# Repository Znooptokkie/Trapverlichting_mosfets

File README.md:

# Automatische trapverlichting

Een automatisch trapverlichtingssysteem op basis van een Raspberry Pi Pico 2 en MicroPython. Het systeem gebruikt twee PIR-bewegingssensoren om beweging te detecteren en stuurt drie dimbare lampen aan via PWM.

De lampen gaan geleidelijk aan en uit. De volgorde waarin de lampen aangaan, is afhankelijk van welke sensor beweging detecteert.

## Functionaliteiten

- Automatische verlichting met twee bewegingssensoren.
- Aansturing van drie afzonderlijke lampen.
- Geleidelijke in- en uitschakeling met PWM.
- Lampen gaan met een instelbare vertraging achter elkaar aan.
- Verschillende inschakelvolgordes afhankelijk van de geactiveerde sensor.
- Instelbare brandduur op maximale helderheid.

## Hardware

- Raspberry Pi Pico 2
- 2x HC-SR505 PIR-bewegingssensor
- 3x dimbare 24V-lamp
- Mean Well LRS-100-24 voeding
- DC-DC buckconverter
- 3x N-kanaal-MOSFET
- Gateweerstanden en pull-downweerstanden
- Zekering en aansluitmateriaal

Zie [hardware.md](hardware.md) voor de onderdelenlijst en [wiring.md](wiring.md) voor de aansluitingen.

## Software

Het project maakt gebruik van MicroPython.

- `main.py`: start het programma en schakelt de lampen uit wanneer het programma handmatig wordt gestopt.
- `lamps.py`: configureert de sensoren en PWM-uitgangen en regelt de verlichting.

## Instellingen

De belangrijkste instellingen staan in `lamps.py`.

| Instelling | Betekenis | Huidige waarde |
|---|---|---:|
| `STEP` | Helderheidsstap per iteratie | 500 |
| `KEEP_SECS_ON` | Brandduur op maximale helderheid | 20 seconden |
| PWM-frequentie | Frequentie van het PWM-signaal | 1000 Hz |
| Fade-interval | Wachttijd tussen helderheidsstappen | 0,025 seconden |
| Sensorinterval | Wachttijd tussen controles | 0,01 seconden |

## Werking

### Sensor 1

1. Sensor 1 detecteert beweging.
2. Lamp 1 gaat als eerste aan, gevolgd door lamp 2 en lamp 3.
3. De lampen blijven gedurende de ingestelde tijd op maximale helderheid branden.
4. Alle lampen dimmen geleidelijk uit.

### Sensor 2

1. Sensor 2 detecteert beweging.
2. Lamp 3 gaat als eerste aan, gevolgd door lamp 2 en lamp 1.
3. De lampen blijven gedurende de ingestelde tijd op maximale helderheid branden.
4. Alle lampen dimmen geleidelijk uit.

Tijdens een actieve verlichtingscyclus worden beide sensoren tijdelijk niet opnieuw uitgelezen. Nieuwe beweging wordt daardoor genegeerd totdat de cyclus is afgelopen.

## GPIO-aansluitingen

| Onderdeel | GPIO |
|---|---|
| Bewegingssensor 1 | GP16 |
| Bewegingssensor 2 | GP22 |
| Lamp 1 | GP18 |
| Lamp 2 | GP19 |
| Lamp 3 | GP20 |

## Documentatie en PCB

De map `docs/images/` bevat afbeeldingen van het hardwareontwerp en de PCB.

- `docs/images/mosfet_pico_schema.png`: afbeelding van het elektrische schema.
- `docs/images/mosfet_pico_pcb.png`: afbeelding van de PCB-layout.
- `docs/images/mosfet_pico_3d.png`: 3D-weergave van de PCB.

De oorspronkelijke KiCad-projectbestanden staan in `hardware/kicad/`:

- `hardware/kicad/mosfet_pico.kicad_pro`: projectinstellingen.
- `hardware/kicad/mosfet_pico.kicad_sch`: elektrisch schema.
- `hardware/kicad/mosfet_pico.kicad_pcb`: PCB-ontwerp.

De Gerber-bestanden staan in `hardware/production/`. Deze bestanden kunnen worden gebruikt om de PCB bij een PCB-fabrikant te laten produceren.

## Bekende aandachtspunten

De sensor-GPIO's kunnen een ongedefinieerde waarde uitlezen wanneer een sensor of signaaldraad wordt losgekoppeld. Om dit te voorkomen, moeten externe pull-downweerstanden van 10 kΩ worden geplaatst tussen de sensor-GPIO's en GND.

- GP16: pull-downweerstand van 10 kΩ naar GND toevoegen.
- GP22: pull-downweerstand van 10 kΩ naar GND toevoegen.

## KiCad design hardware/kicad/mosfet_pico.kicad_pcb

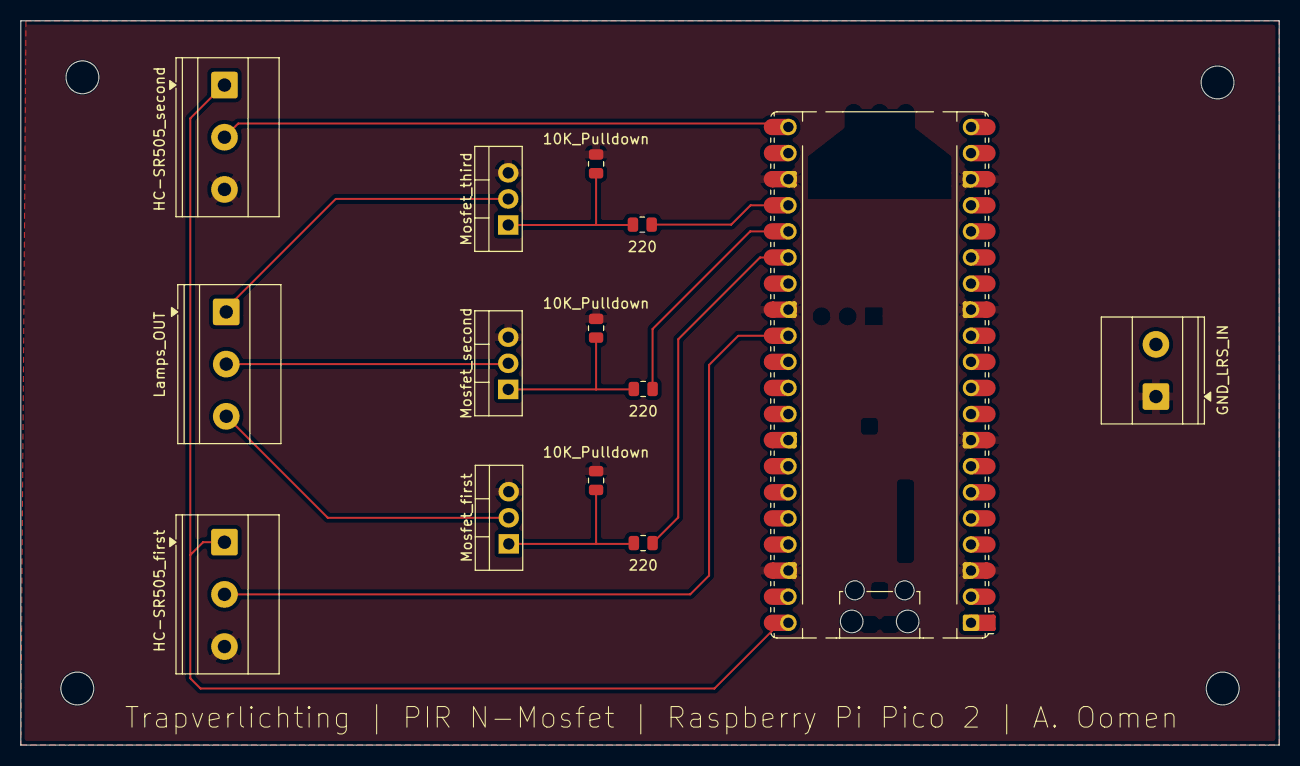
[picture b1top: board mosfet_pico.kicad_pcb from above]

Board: 2 copper layers, 122.5 x 70.5 mm, 14 parts (0 on the bottom side), 13 nets.

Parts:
10K_Pulldown, 10K_Pulldown#2, 10K_Pulldown#3: 10k; R_0805_2012Metric
220, 220#2, 220#3: 220; R_0805_2012Metric
A1: RaspberryPi_Pico; RaspberryPi_Pico_Common_Unspecified
GND_LRS_IN: Screw_Terminal_01x02; TerminalBlock_Phoenix_MKDS-1,5-2-5.08_1x02_P5.08mm_Horizont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
HC-SR505_first, HC-SR505_second: Screw_Terminal_01x03; TerminalBlock_Phoenix_MKDS-1,5-3-5.08_1x03_P5.08mm_Horizont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
Lamps_OUT: Screw_Terminal_01x03; TerminalBlock_Phoenix_MKDS-1,5-3-5.08_1x03_P5.08mm_Horizont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
Mosfet_first: NMOS; TO-220-3_Vertical
Mosfet_second: NMOS; TO-220-3_Vertical
Mosfet_third: NMOS; TO-220-3_Vertical

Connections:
+5V: A1.40 (VBUS), HC-SR505_first.1, HC-SR505_second.1
GND: 10K_Pulldown.1, 10K_Pulldown#2.1, 10K_Pulldown#3.1, A1.3 (GND), A1.8 (GND), A1.13 (GND), A1.18 (GND), A1.23 (GND), A1.28 (GND), A1.38 (GND), GND_LRS_IN.1 (Pin_1_1), HC-SR505_first.3, HC-SR505_second.3, Mosfet_first.3 (S), Mosfet_second.3 (S), Mosfet_third.3 (S)
unnamed: A1.21 (GPIO16), HC-SR505_second.2
unnamed: 220#3.1, A1.24 (GPIO18)
unnamed: 220#2.1, A1.25 (GPIO19)
unnamed: 220.1, A1.26 (GPIO20)
unnamed: A1.29 (GPIO22), HC-SR505_first.2
unnamed: Lamps_OUT.1, Mosfet_third.2 (D)
unnamed: Lamps_OUT.2, Mosfet_second.2 (D)
unnamed: Lamps_OUT.3, Mosfet_first.2 (D)
unnamed: 10K_Pulldown#3.2, 220.2, Mosfet_first.1 (G)
unnamed: 10K_Pulldown#2.2, 220#2.2, Mosfet_second.1 (G)
unnamed: 10K_Pulldown.2, 220#3.2, Mosfet_third.1 (G)
